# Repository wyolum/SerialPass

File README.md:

# SerialPass
simple Serial pass through board - Serial In to Serial Out with break out pads to probe serial signals

License
-------
[CERN Open Hardware Licence v1.2 ]

[CERN Open Hardware Licence v1.2 ]:http://www.ohwr.org/attachments/2388/cern_ohl_v_1_2.txt

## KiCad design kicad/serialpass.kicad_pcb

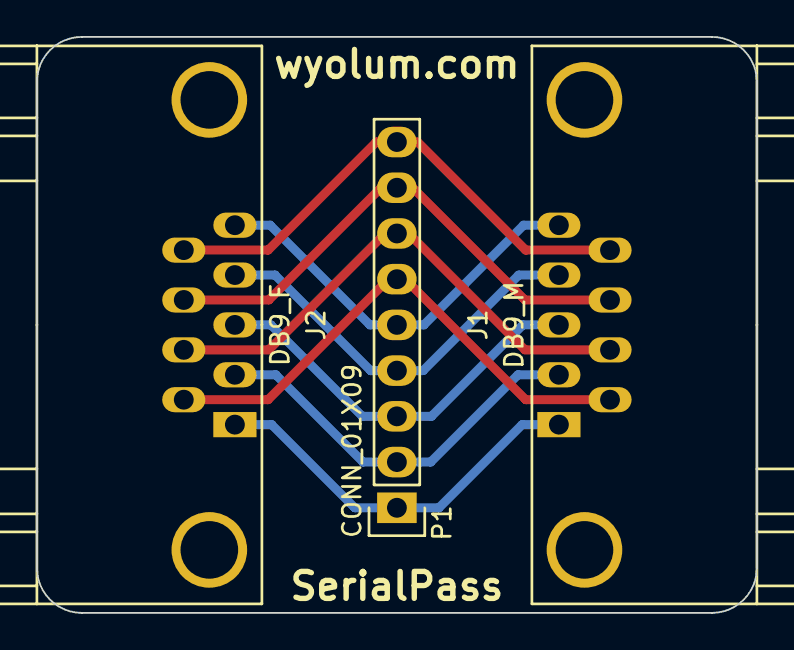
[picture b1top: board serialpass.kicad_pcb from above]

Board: 2 copper layers, 40.0 x 32.0 mm, 3 parts (0 on the bottom side), 9 nets.

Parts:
J1: DB9_M; DB9MC
J2: DB9_F; DB9FC
P1: CONN_01X09; Pin_Header_Straight_1x09

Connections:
unnamed: J1.1, J2.1, P1.1
unnamed: J1.2, J2.2, P1.2
unnamed: J1.3, J2.3, P1.3
unnamed: J1.4, J2.4, P1.4
unnamed: J1.5, J2.5, P1.5
unnamed: J1.6, J2.6, P1.6
unnamed: J1.7, J2.7, P1.7
unnamed: J1.8, J2.8, P1.8
unnamed: J1.9, J2.9, P1.9

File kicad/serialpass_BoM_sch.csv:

Reference, Value, Footprint, Datasheet
J1,DB9_M,Connect:DB9FC,
J2,DB9_F,Connect:DB9MC,
P1,CONN_01X09,Pin_Headers:Pin_Header_Straight_1x09,

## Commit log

2015-03-12 SerialPass gerbers ready
